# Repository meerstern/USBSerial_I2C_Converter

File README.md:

# USBシリアルI2C変換基板
USB Serial I2C Converter

## 概要 
  * USBシリアルをI2Cマスタに変換する基板です
  * シリアルCOMポートを介してPCやRPI等からI2Cデバイスを制御できます  
  * I2Cデバイスの動作確認やラピッドプロトタイピングに最適です  
  * シリアルCOM変換にPL2303GL、シリアルI2C変換に[SC18IM704][1]を使用しています(V2：現行モデル)  
  * シリアルCOM変換にPL2303SA、シリアルI2C変換にSC18IM700を使用しています(V1：旧モデル)  
  * TeratermやNode-Red、Unity、Python等からシリアルCOMポートを介して容易なコマンドでI2Cデバイスを制御できます  
  * I2CはGrove互換コネクタを搭載しています  
  * Grove互換コネクタの電源、プルアップ抵抗はスイッチ切り替えで5V/3.3Vに対応しています  
    ※USB、I2Cデバイスを接続する前に基板上のシルクを確認してから5V/3.3V切替してください  
    ※3.3V専用デバイスに5Vを加えないように注意してください  

## 詳細 
 * シリアルI2C変換SC18IM700/SC18IM704のコマンドは[データシート(PDF)][8]を参照してください  
 * シリアルI2C変換[SC18IM700/SC18IM704][1]のデフォルトボーレートは9600bpsです  
 * アドレスの異なる複数のデバイスを接続する場合は[I2Cハブ][7]を使用してください
 * 基板のピンヘッダを用いることでSC18IM700/SC18IM704単体の変換基板としても使用できます  
 * USB5V電源入力側に350mA定格のリセッタブルヒューズを搭載しています  
 * 給電可能な電流は3.3Vラインで最大150mA前後、5Vラインで最大350mAです
 * コマンドの応答がない場合はピンセット等でRSTピンとGNDピンを1秒程度短絡してリセットさせてください    

## USBドライバ
 * Windows版は[こちらからダウンロード][2]して使用してください  
 ※標準ドライバではNode-Redで動作不具合があるため、最新のドライバに更新し、再起動後に使用してください
 * Mac版は標準でドライバが読み込まれますが、必要に応じて[こちらからダウンロード][3]して使用してください  
 * Linux版はKernel 2.4.31以降、標準でドライバが組み込まれています  

## Node-Redサンプルフロー
 * シリアルポートフローを使用して[Grove温湿度センサSHT31][5]から温度、湿度を読み込む[サンプル][4]  
 * 温湿度センサ　SHT31、I2C接続LCD AQM1602、マルチ環境センサBME280、CO2センサ CCS811、リアルタイムクロック DS1307、AD変換 MCP3425、粒子センサ HM3301、赤外線グリッドセンサAMG8833、I2Cデバイス検索のサンプルコードがあります  
 ※詳細はサンプルコードをご確認ください  
 ※シリアルポートフローを使用する場合はオンプレミス版Node-Redを使用する必要があります。[こちらの記事][6]を参考にしてください  

## Teratermサンプルマクロ
 * サンプルマクロを実行する際には必ず言語設定を「English」、「Default.lng」に設定してください。正しく送受信されません。  

## WebシリアルAPIツール
 * WebシリアルAPIを使用した[ツールを公開][9]しています  
 * EdgeもしくはChromeブラウザからアクセスすると簡単にI2Cデバイスと通信できます  
 * 対応デバイスは随時追加予定です  

## 変換基板
 * USBシリアルI2C変換基板の外観  

 ※上記写真は試作基板のため、量産版と異なる場合があります  
 
 ## 販売サイト
  * [スイッチサイエンス][10]
  
 ## 告知
  * SC18IM700、PL2303SAは生産完了のため、23年7月以降はそれぞれ後継機種のSC18IM704、PL2303GLを使用したv2.x基板に変更しました
  * SC18IM700/SC18IM704の基本的なI2Cコマンド等は互換性が維持されています
  * 生産完了に伴い、v1.xモデルの製造及び販売は終了しました  

# USB Serial I2C Converter
## Overview 

  * This is a board that converts USB serial to I2C master.
  * Can control I2C devices from PC, RPI, etc. via serial COM port
  * Ideal for I2C device operation verification and rapid prototyping
  * PL2303GL is used for serial COM conversion, and [SC18IM704][1] is used for serial I2C conversion (V2: current model)
  * Control I2C devices with easy commands via serial COM port from Teraterm, Node-Red, Unity, Python, etc.
  * I2C has Grove compatible connector  
  * Grove compatible connector power supply and pull-up resistor support 5V/3.3V by switching
  * Before connecting USB or I2C devices, please check the silk on the board and then switch 5V/3.3V.
  * Please be careful not to apply 5V to 3.3V only devices.

## Details 
  * For serial I2C conversion SC18IM700/SC18IM704 commands, please refer to [Datasheet (PDF)][8]
  * The default baud rate for serial I2C conversion [SC18IM700/SC18IM704][1] is 9600bps
  * When connecting multiple devices with different addresses, please use [I2C hub][7]
  * Can also be used as a conversion board for SC18IM700/SC18IM704 by using the pin header on the board
  * Equipped with a resettable fuse rated at 350mA on the USB5V power input side
  * The maximum current that can be supplied is around 150mA for 3.3V line, and 350mA for 5V line.
  * If there is no response to the command, short the RST pin and GND pin with tweezers for about 1 second to reset.

  ## USB Driver
  * For Windows version, please [download][2] from here.
  * The standard driver has a malfunction with Node-Red, so please update to the latest driver and use it after restarting.
  * The driver is loaded by default in the Mac version, but if necessary, please [download][3].
  * The Linux version has a built-in driver as standard since Kernel 2.4.31 

 ## Node-Red Sample Flow
  * Read temperature and humidity from [Grove temperature and humidity sensor SHT31][5] using serial port flow [sample][4]
  * Temperature and humidity sensor SHT31, I2C connection LCD AQM1602, multi-environment sensor BME280, CO2 sensor CCS811, real-time clock DS1307, AD conversion MCP3425, particle sensor HM3301, infrared grid sensor AMG8833, sample code for I2C device search is available
  * Please check the sample code for details.
  * If you want to use serial port flow, you need to use the on-premises version of Node-Red. Please refer to [this article(Japanese)][6]

## Teraterm Sample Macro
 * When running the sample macro, be sure to set the language settings to "English" and "Default.lng". It will not be sent or received correctly.

## Web Serial API Tools
 * [Publishing tools][11] using Web Serial API
 * Easily communicate with I2C devices when accessed from Edge or Chrome browsers
 * Compatible devices will be added

 ## Announcement
  * Production of SC18IM700 and PL2303SA has been discontinued, so from July 2023 onwards, we have changed to v2.x boards using the successor models SC18IM704 and PL2303GL, respectively.
  * Compatibility of basic I2C commands etc. of SC18IM700/SC18IM704 is maintained.
  * Due to the completion of production, the manufacture and sale of v1.x model has ended.

[1]: https://www.nxp.jp/part/SC18IM704PW#/
[2]: https://www.prolific.com.tw/UserFiles/files/PL23XX_Prolific_DriverInstaller_v408.zip
[3]: https://www.prolific.com.tw/UserFiles/files/PL2303HXD_G_Mac%20Driver_v2_1_0_20210311.zip
[4]: https://github.com/meerstern/USBSerial_I2C_Converter/tree/master/SampleNodeRedFlow
[5]: https://www.switch-science.com/catalog/2853/
[6]: http://meerstern.seesaa.net/article/465007276.html
[7]: https://www.switch-science.com/catalog/796/
[8]: https://www.nxp.jp/docs/en/data-sheet/SC18IM704.pdf
[9]: https://meerstern.github.io/
[10]: https://www.switch-science.com/products/6214
[11]: https://meerstern.github.io/Web%20API%20Tools_En.html

MIT Lisense

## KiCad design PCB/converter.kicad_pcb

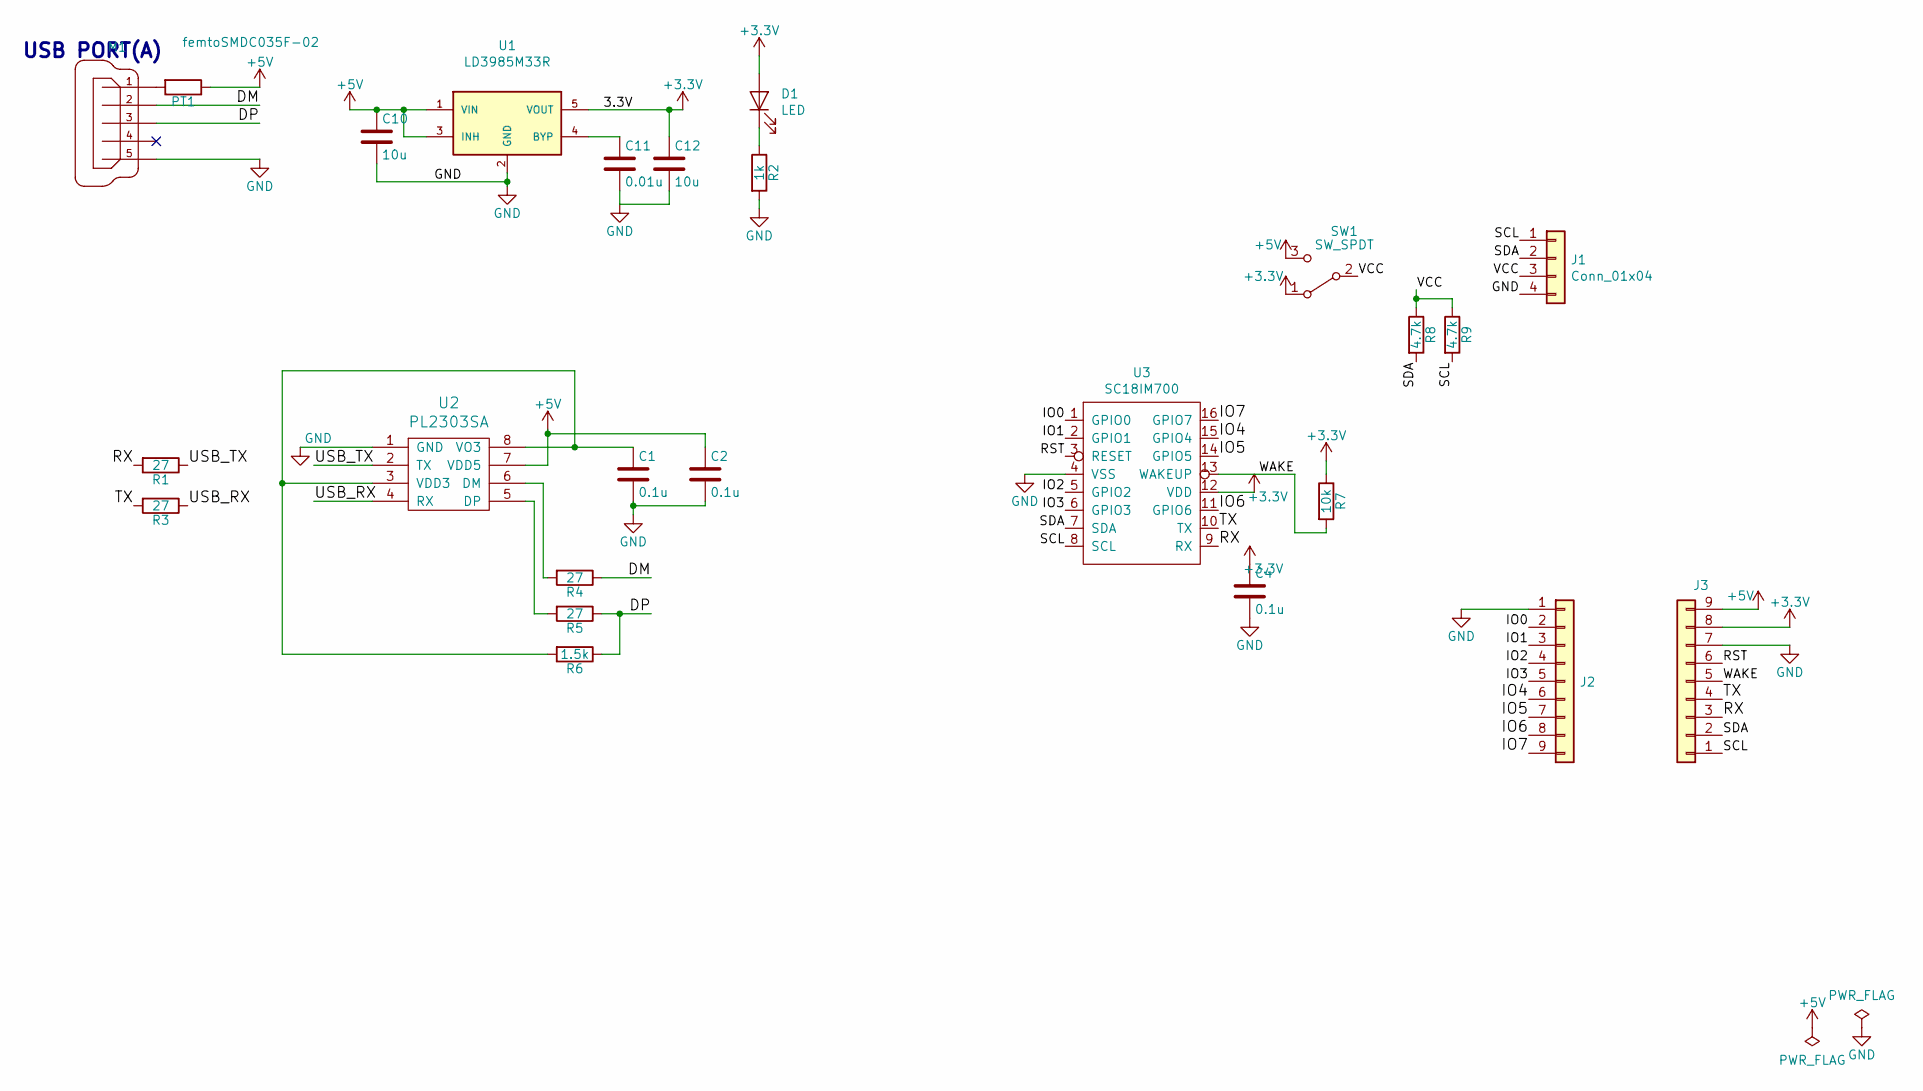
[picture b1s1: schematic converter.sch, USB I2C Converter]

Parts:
C1, C2, C4: 0.1u; C_0603_1608Metric
C10, C12: 10u; C_0805_2012Metric
C11: 0.01u; C_0603_1608Metric
D1: LED; LED_0603_1608Metric
J1: Conn_01x04; GROVE
J2, J3: Conn_01x09; PinSocket_1x09_P2.54mm_Vertical
M1: MICRO-USB-ZX62R-B-5P-con-hirose; CONN-10118194-0001LF-FCI
PT1: femtoSMDC035F-02; R_0603_1608Metric
R1, R3, R4, R5: 27; R_0603_1608Metric
R2: 1k; R_0603_1608Metric
R6: 1.5k; R_0603_1608Metric
R7: 10k; R_0603_1608Metric
R8, R9: 4.7k; R_0603_1608Metric
SW1: SW_SPDT; DPDT_SMD
U1: LD3985M33R; SOT-23-5
U2: PL2303SA; SOIC-8_3.9x4.9mm_P1.27mm
U3: SC18IM700; TSSOP-16_4.4x5mm_P0.65mm

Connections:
+3V3: C4.1, C12.1, D1.2 (A), J3.8, R7.1, SW1.1 (A), U1.5 (VOUT), U3.12 (VDD)
+5V: C2.1, C10.1, J3.9, PT1.1, SW1.3 (C), U1.1 (VIN), U1.3 (INH), U2.7 (VDD5)
/DM: M1.2, R4.1
/DP: M1.3, R5.1, R6.1
/IO0: J2.2, U3.1 (GPIO0)
/IO1: J2.3, U3.2 (GPIO1)
/IO2: J2.4, U3.5 (GPIO2)
/IO3: J2.5, U3.6 (GPIO3)
/IO4: J2.6, U3.15 (GPIO4)
/IO5: J2.7, U3.14 (GPIO5)
/IO6: J2.8, U3.11 (GPIO6)
/IO7: J2.9, U3.16 (GPIO7)
/RST: J3.6, U3.3 (RESET)
/RX: J3.3, R1.2, U3.9 (RX)
/SCL: J1.1, J3.1, R9.2, U3.8 (SCL)
/SDA: J1.2, J3.2, R8.2, U3.7 (SDA)
/TX: J3.4, R3.2, U3.10 (TX)
/USB_RX: R3.1, U2.4 (RX)
/USB_TX: R1.1, U2.2 (TX)
/VCC: J1.3, R8.1, R9.1, SW1.2 (B)
/WAKE: J3.5, R7.2, U3.13 (WAKEUP)
GND: C1.2, C2.2, C4.2, C10.2, C11.2, C12.2, J1.4, J2.1, J3.7, M1.5, R2.2, U1.2 (GND), U2.1 (GND), U3.4 (VSS)
unnamed: C1.1, R6.2, U2.3 (VDD3), U2.8 (VO3)
unnamed: C11.1, U1.4 (BYP)
unnamed: D1.1 (K), R2.1
unnamed: M1.1, PT1.2
unnamed: R4.2, U2.6 (DM)
unnamed: R5.2, U2.5 (DP)

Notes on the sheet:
USB PORT(A)

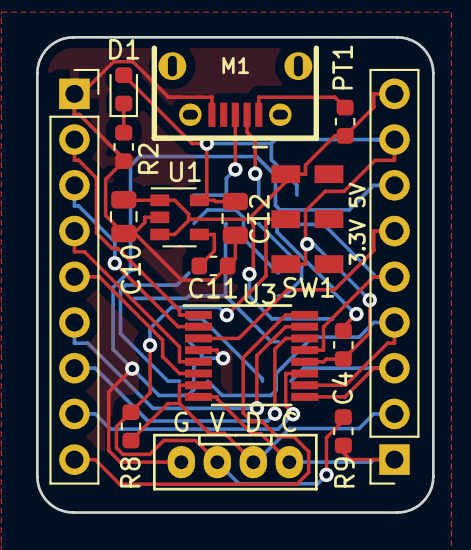
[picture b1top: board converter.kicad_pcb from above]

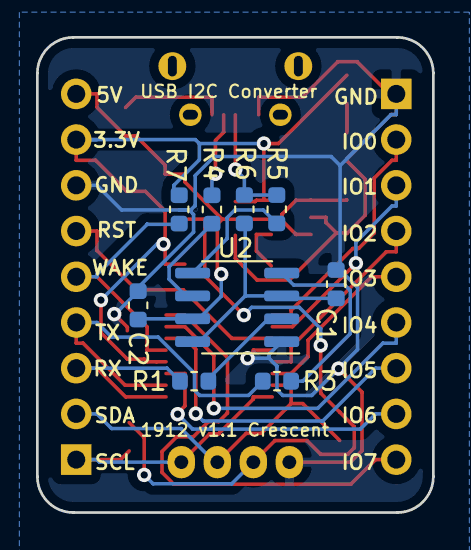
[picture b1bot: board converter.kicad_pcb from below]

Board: 2 copper layers, 22.0 x 26.4 mm, 25 parts (9 on the bottom side), 28 nets.

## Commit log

2020-01-05 Init upload
2020-01-05 Fix URL Link
2020-01-11 Add Sample Code
    MCP3425、AQM1602、I2C Device search
2020-01-14 Add sample flow of CCS811 CO2 sensor
2020-01-21 Add Node-Red Code for particle sensor, HM3301
2020-01-23 add images
2020-01-26 Add BME280 flows
2020-01-26 Rename
2020-01-26 Add files
2020-01-31 Add sample code for AMG8833
2020-02-11 Add EEPROM sample and VL53L0 sample
2020-02-22 Add VL53L1 & GPIO samples
2020-03-08 Add MLX90614 sample flow
2020-04-07 Add Pressure sensor of LPS22HH from ST
2020-04-14 Add AMS Angle Sensor AS5600, AS5601
2020-06-14 Add CO2 sensor with SGP30
2020-08-22 Add flows for ADC121C021
2020-09-21 Add NodeJSPortable
2021-08-17 Add flow of RTC RV-8803-C7
2022-03-01 Add I2C Timeout Setting
2022-03-01 Add Reg Clear Function
2022-03-09 Add Python Sample Code for Python3
2022-08-22 Updated Driver Link
2023-08-01 Add pcb files for V2
